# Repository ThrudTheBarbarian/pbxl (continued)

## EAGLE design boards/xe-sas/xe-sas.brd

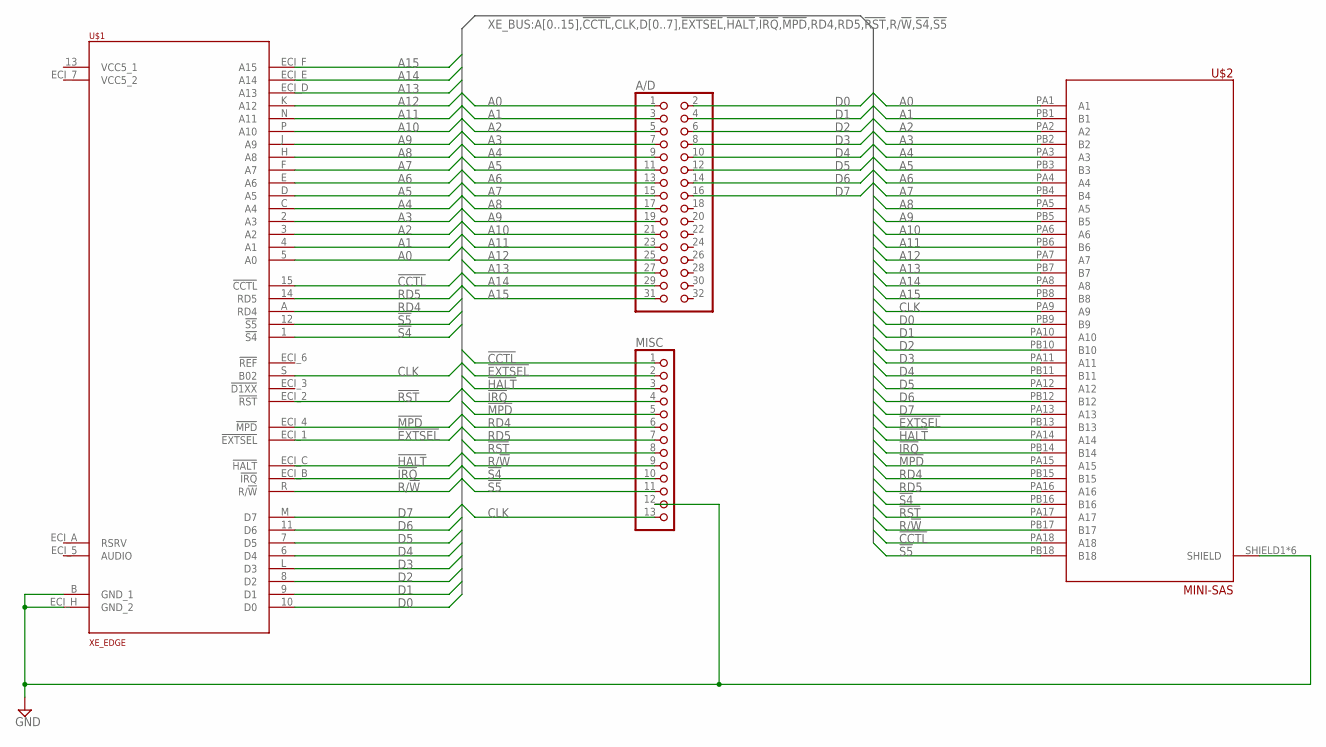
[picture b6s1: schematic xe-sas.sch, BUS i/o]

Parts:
A/D: PINHD-2X16; 2X16
MISC: PINHD-1X13; 1X13
U$1: XE_EDGE
U$2: MINI-SAS

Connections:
!CCTL!: MISC.1, U$1.15 (!CCTL!), U$2.PA18 (A18)
!EXTSEL!: MISC.2, U$1.ECI_1 (!EXTSEL!), U$2.PB13 (B13)
!HALT!: MISC.3, U$1.ECI_C (!HALT!), U$2.PA14 (A14)
!IRQ!: MISC.4, U$1.ECI_B (!IRQ!), U$2.PB14 (B14)
!MPD!: MISC.5, U$1.ECI_4 (!MPD!), U$2.PA15 (A15)
!RST!: MISC.8, U$1.ECI_2 (!RST!), U$2.PA17 (A17)
!S4!: MISC.10, U$1.1 (!S4!), U$2.PB16 (B16)
!S5!: MISC.11, U$1.12 (!S5!), U$2.PB18 (B18)
A0: A/D.1, U$1.5 (A0), U$2.PA1 (A1)
A1: A/D.3, U$1.4 (A1), U$2.PB1 (B1)
A2: A/D.5, U$1.3 (A2), U$2.PA2 (A2)
A3: A/D.7, U$1.2 (A3), U$2.PB2 (B2)
A4: A/D.9, U$1.C (A4), U$2.PA3 (A3)
A5: A/D.11, U$1.D (A5), U$2.PB3 (B3)
A6: A/D.13, U$1.E (A6), U$2.PA4 (A4)
A7: A/D.15, U$1.F (A7), U$2.PB4 (B4)
A8: A/D.17, U$1.H (A8), U$2.PA5 (A5)
A9: A/D.19, U$1.J (A9), U$2.PB5 (B5)
A10: A/D.21, U$1.P (A10), U$2.PA6 (A6)
A11: A/D.23, U$1.N (A11), U$2.PB6 (B6)
A12: A/D.25, U$1.K (A12), U$2.PA7 (A7)
A13: A/D.27, U$1.ECI_D (A13), U$2.PB7 (B7)
A14: A/D.29, U$1.ECI_E (A14), U$2.PA8 (A8)
A15: A/D.31, U$1.ECI_F (A15), U$2.PB8 (B8)
CLK: MISC.13, U$1.S (B02), U$2.PA9 (A9)
D0: A/D.2, U$1.10 (D0), U$2.PB9 (B9)
D1: A/D.4, U$1.9 (D1), U$2.PA10 (A10)
D2: A/D.6, U$1.8 (D2), U$2.PB10 (B10)
D3: A/D.8, U$1.L (D3), U$2.PA11 (A11)
D4: A/D.10, U$1.6 (D4), U$2.PB11 (B11)
D5: A/D.12, U$1.7 (D5), U$2.PA12 (A12)
D6: A/D.14, U$1.11 (D6), U$2.PB12 (B12)
D7: A/D.16, U$1.M (D7), U$2.PA13 (A13)
GND: MISC.12, U$1.B (GND_1), U$1.ECI_H (GND_2), U$2.SHIELD1 (SHIELD), U$2.SHIELD2 (SHIELD), U$2.SHIELD3 (SHIELD), U$2.SHIELD4 (SHIELD), U$2.SHIELD5 (SHIELD), U$2.SHIELD6 (SHIELD)
R/!W!: MISC.9, U$1.R (R/!W!), U$2.PB17 (B17)
RD4: MISC.6, U$1.A (RD4), U$2.PB15 (B15)
RD5: MISC.7, U$1.14 (RD5), U$2.PA16 (A16)

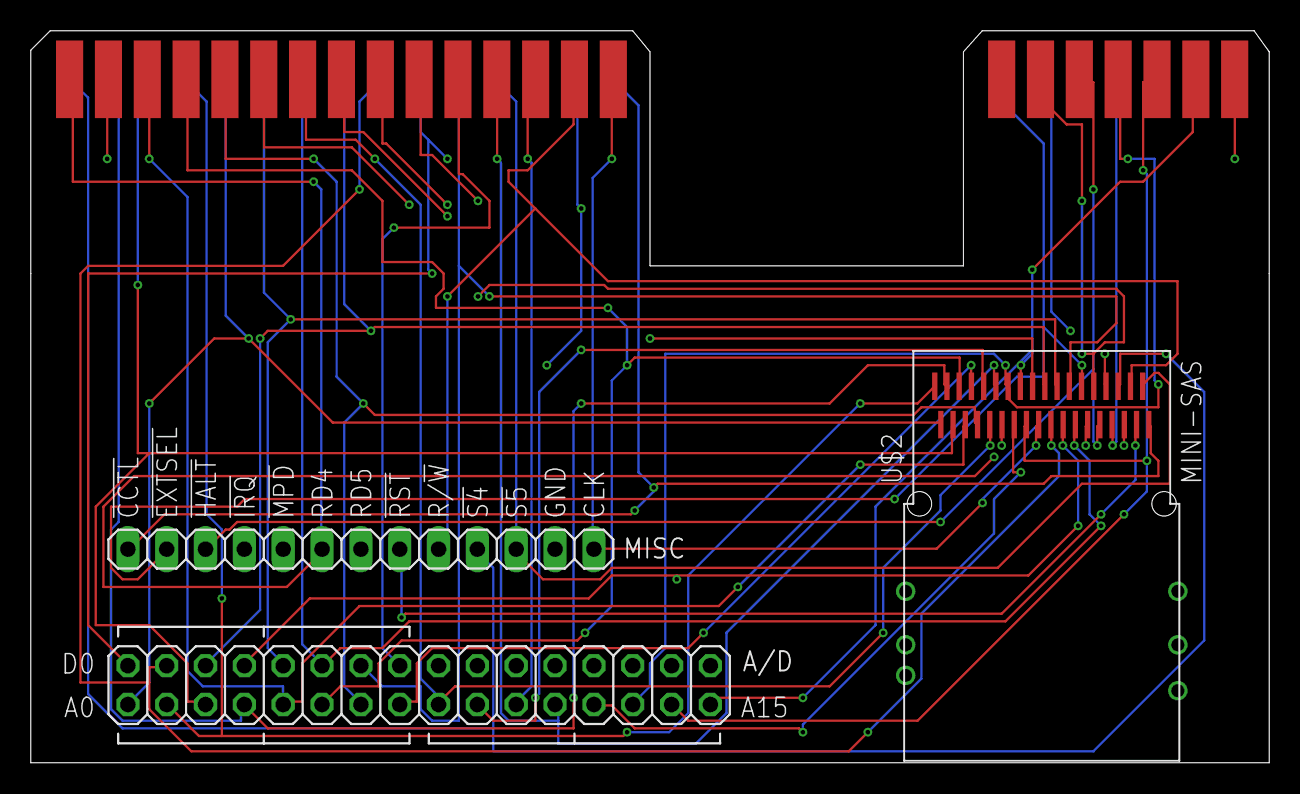
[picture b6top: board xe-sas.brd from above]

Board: 4 copper layers, 81.0 x 47.9 mm, 4 parts (0 on the bottom side), 37 nets.

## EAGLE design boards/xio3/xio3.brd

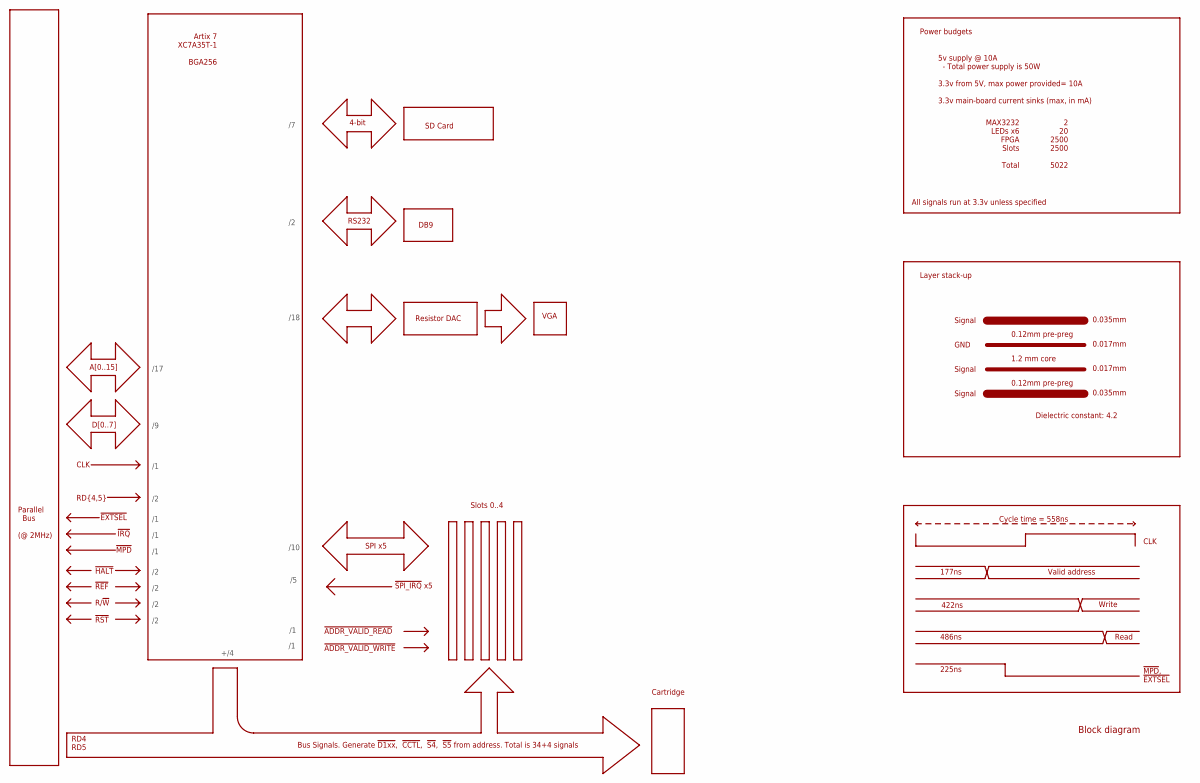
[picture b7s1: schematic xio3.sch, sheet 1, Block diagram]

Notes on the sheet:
Slots 0..4
Bus Signals. Generate !D1xx!, !CCTL!, !S4!, !S5! from address. Total is 34+4 signals
RS232
SD Card
DB9
5v supply @ 10A - Total power supply is 50W 3.3v from 5V, max power provided= 10A 3.3v main-board current sinks (max, in mA)
MAX3232 LEDs x6 FPGA Slots Total
2 20 2500 2500 5022
1.2 mm core
0.12mm pre-preg
0.035mm
0.017mm
Layer stack-up
GND
Dielectric constant: 4.2
Cycle time = 558ns
Valid address
Write
Read
177ns
422ns
486ns
225ns
!MPD!, !EXTSEL!
CLK
Power budgets
Artix 7 XC7A35T-1 BGA256
Resistor DAC
VGA
4-bit
Signal
Block diagram
Parallel Bus (@ 2MHz)
A[0..15]
D[0..7]
RD{4,5}
!MPD!
!IRQ!
!EXTSEL!
!HALT!

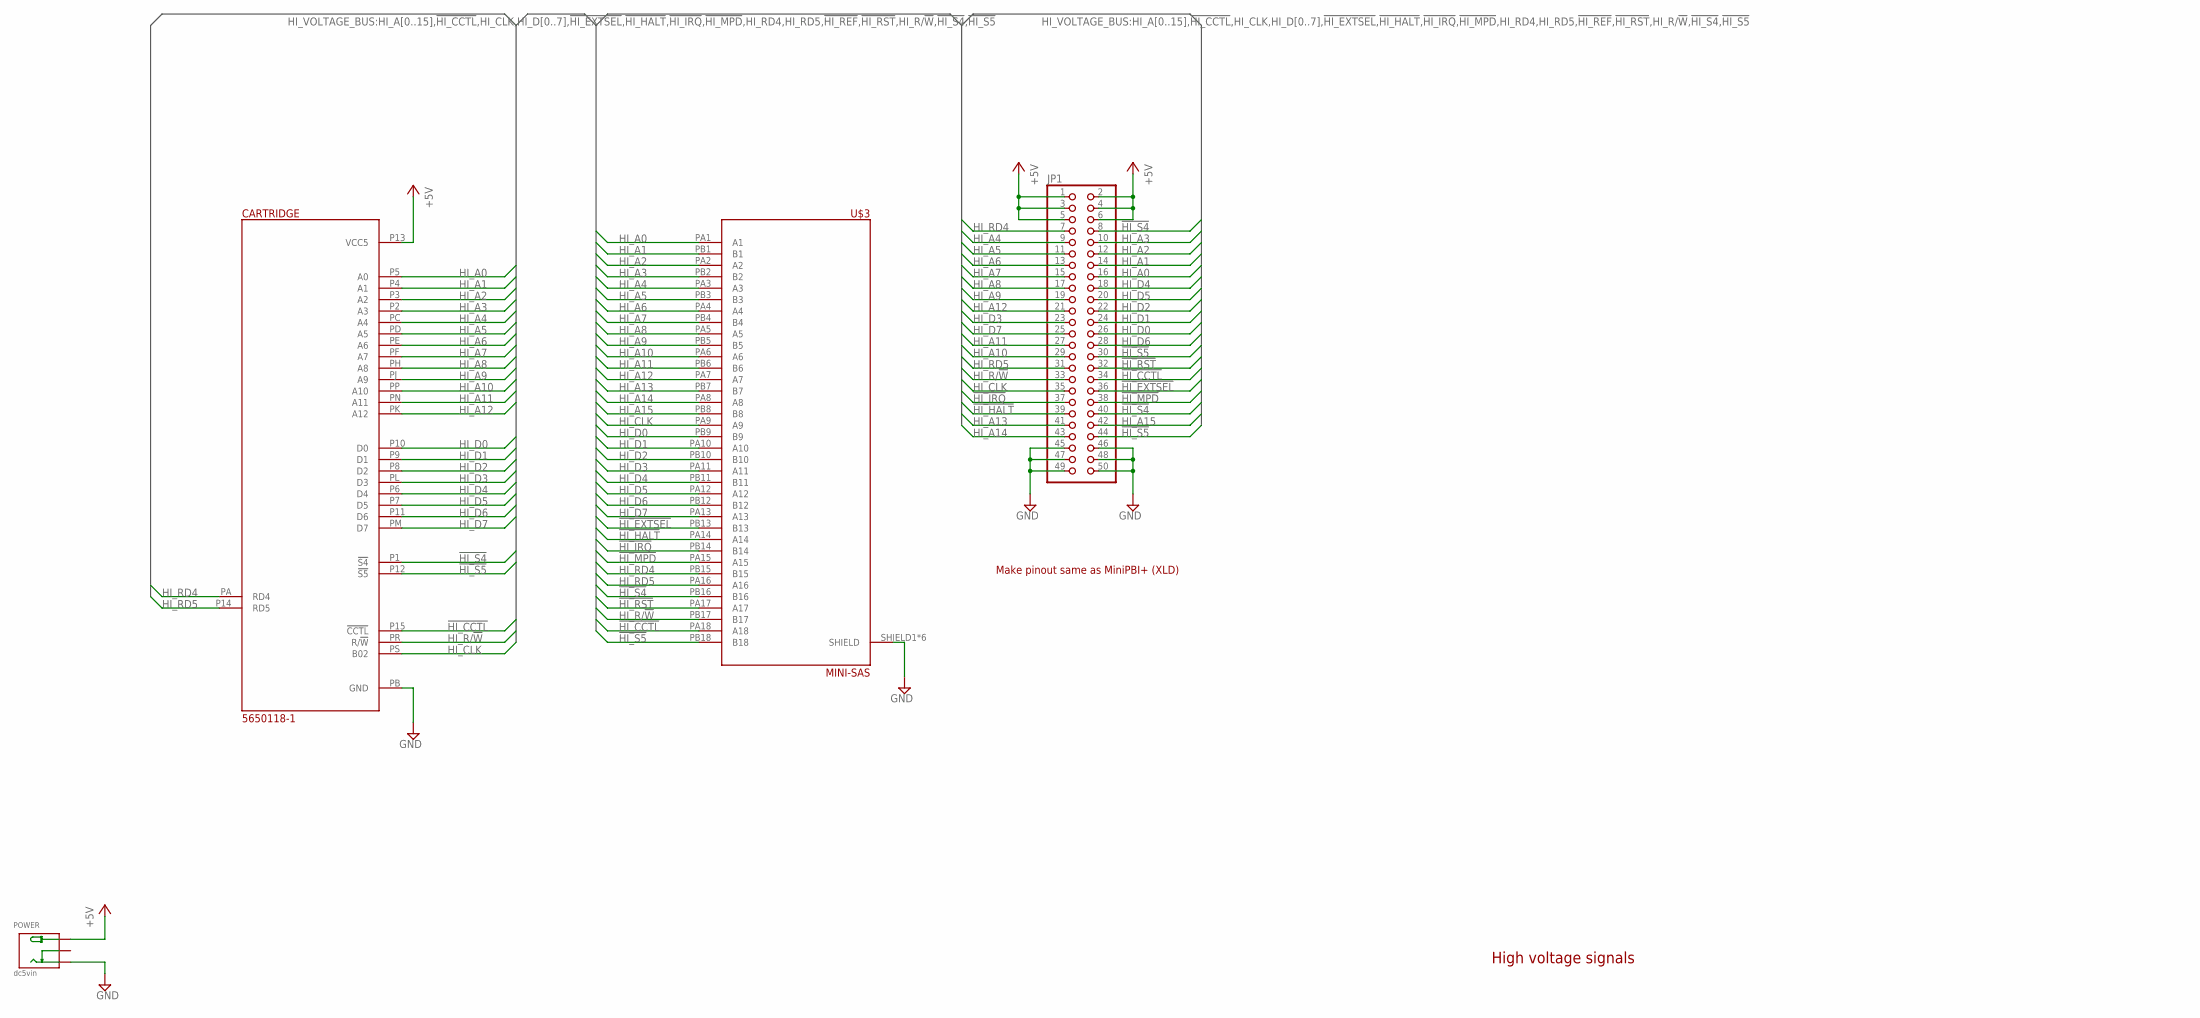
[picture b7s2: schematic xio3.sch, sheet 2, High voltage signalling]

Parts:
CARTRIDGE: 5650118-1; A8_CART
JP1: PINHD-2X25; 2X25
POWER: dc5vin; DCJ3P-14.2X11.0X9.0MM
U$3: MINI-SAS

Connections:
!HI_CCTL!: CARTRIDGE.P15 (!CCTL!), JP1.34, U$3.PA18 (A18)
!HI_EXTSEL!: JP1.36, U$3.PB13 (B13); also elsewhere on the board
!HI_HALT!: JP1.39, U$3.PA14 (A14); also elsewhere on the board
!HI_IRQ!: JP1.37, U$3.PB14 (B14); also elsewhere on the board
!HI_MPD!: JP1.38, U$3.PA15 (A15); also elsewhere on the board
!HI_RST!: JP1.32, U$3.PA17 (A17); also elsewhere on the board
!HI_S4!: CARTRIDGE.P1 (!S4!), JP1.8, JP1.40, U$3.PB16 (B16)
!HI_S5!: CARTRIDGE.P12 (!S5!), JP1.30, JP1.44, U$3.PB18 (B18)
+5V: CARTRIDGE.P13 (VCC5), JP1.1, JP1.2, JP1.3, JP1.4, JP1.5, JP1.6, POWER.+; also elsewhere on the board
GND: CARTRIDGE.PB (GND), JP1.45, JP1.46, JP1.47, JP1.48, JP1.49, JP1.50, POWER.-1 (-), U$3.SHIELD1 (SHIELD), U$3.SHIELD2 (SHIELD), U$3.SHIELD3 (SHIELD), U$3.SHIELD4 (SHIELD), U$3.SHIELD5 (SHIELD), U$3.SHIELD6 (SHIELD); also elsewhere on the board
HI_A0: CARTRIDGE.P5 (A0), JP1.16, U$3.PA1 (A1); also elsewhere on the board
HI_A1: CARTRIDGE.P4 (A1), JP1.14, U$3.PB1 (B1); also elsewhere on the board
HI_A2: CARTRIDGE.P3 (A2), JP1.12, U$3.PA2 (A2); also elsewhere on the board
HI_A3: CARTRIDGE.P2 (A3), JP1.10, U$3.PB2 (B2); also elsewhere on the board
HI_A4: CARTRIDGE.PC (A4), JP1.9, U$3.PA3 (A3); also elsewhere on the board
HI_A5: CARTRIDGE.PD (A5), JP1.11, U$3.PB3 (B3); also elsewhere on the board
HI_A6: CARTRIDGE.PE (A6), JP1.13, U$3.PA4 (A4); also elsewhere on the board
HI_A7: CARTRIDGE.PF (A7), JP1.15, U$3.PB4 (B4); also elsewhere on the board
HI_A8: CARTRIDGE.PH (A8), JP1.17, U$3.PA5 (A5); also elsewhere on the board
HI_A9: CARTRIDGE.PJ (A9), JP1.19, U$3.PB5 (B5); also elsewhere on the board
HI_A10: CARTRIDGE.PP (A10), JP1.29, U$3.PA6 (A6); also elsewhere on the board
HI_A11: CARTRIDGE.PN (A11), JP1.27, U$3.PB6 (B6); also elsewhere on the board
HI_A12: CARTRIDGE.PK (A12), JP1.21, U$3.PA7 (A7); also elsewhere on the board
HI_A13: JP1.41, U$3.PB7 (B7); also elsewhere on the board
HI_A14: JP1.43, U$3.PA8 (A8); also elsewhere on the board
HI_A15: JP1.42, U$3.PB8 (B8); also elsewhere on the board
HI_CLK: CARTRIDGE.PS (B02), JP1.35, U$3.PA9 (A9); also elsewhere on the board
HI_D0: CARTRIDGE.P10 (D0), JP1.26, U$3.PB9 (B9); also elsewhere on the board
HI_D1: CARTRIDGE.P9 (D1), JP1.24, U$3.PA10 (A10); also elsewhere on the board
HI_D2: CARTRIDGE.P8 (D2), JP1.22, U$3.PB10 (B10); also elsewhere on the board
HI_D3: CARTRIDGE.PL (D3), JP1.23, U$3.PA11 (A11); also elsewhere on the board
HI_D4: CARTRIDGE.P6 (D4), JP1.18, U$3.PB11 (B11); also elsewhere on the board
HI_D5: CARTRIDGE.P7 (D5), JP1.20, U$3.PA12 (A12); also elsewhere on the board
HI_D6: CARTRIDGE.P11 (D6), JP1.28, U$3.PB12 (B12); also elsewhere on the board
HI_D7: CARTRIDGE.PM (D7), JP1.25, U$3.PA13 (A13); also elsewhere on the board
HI_R/!W!: CARTRIDGE.PR (R/!W!), JP1.33, U$3.PB17 (B17); also elsewhere on the board
HI_RD4: CARTRIDGE.PA (RD4), JP1.7, U$3.PB15 (B15); also elsewhere on the board
HI_RD5: CARTRIDGE.P14 (RD5), JP1.31, U$3.PA16 (A16); also elsewhere on the board

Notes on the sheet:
High voltage signals
Make pinout same as MiniPBI+ (XLD)

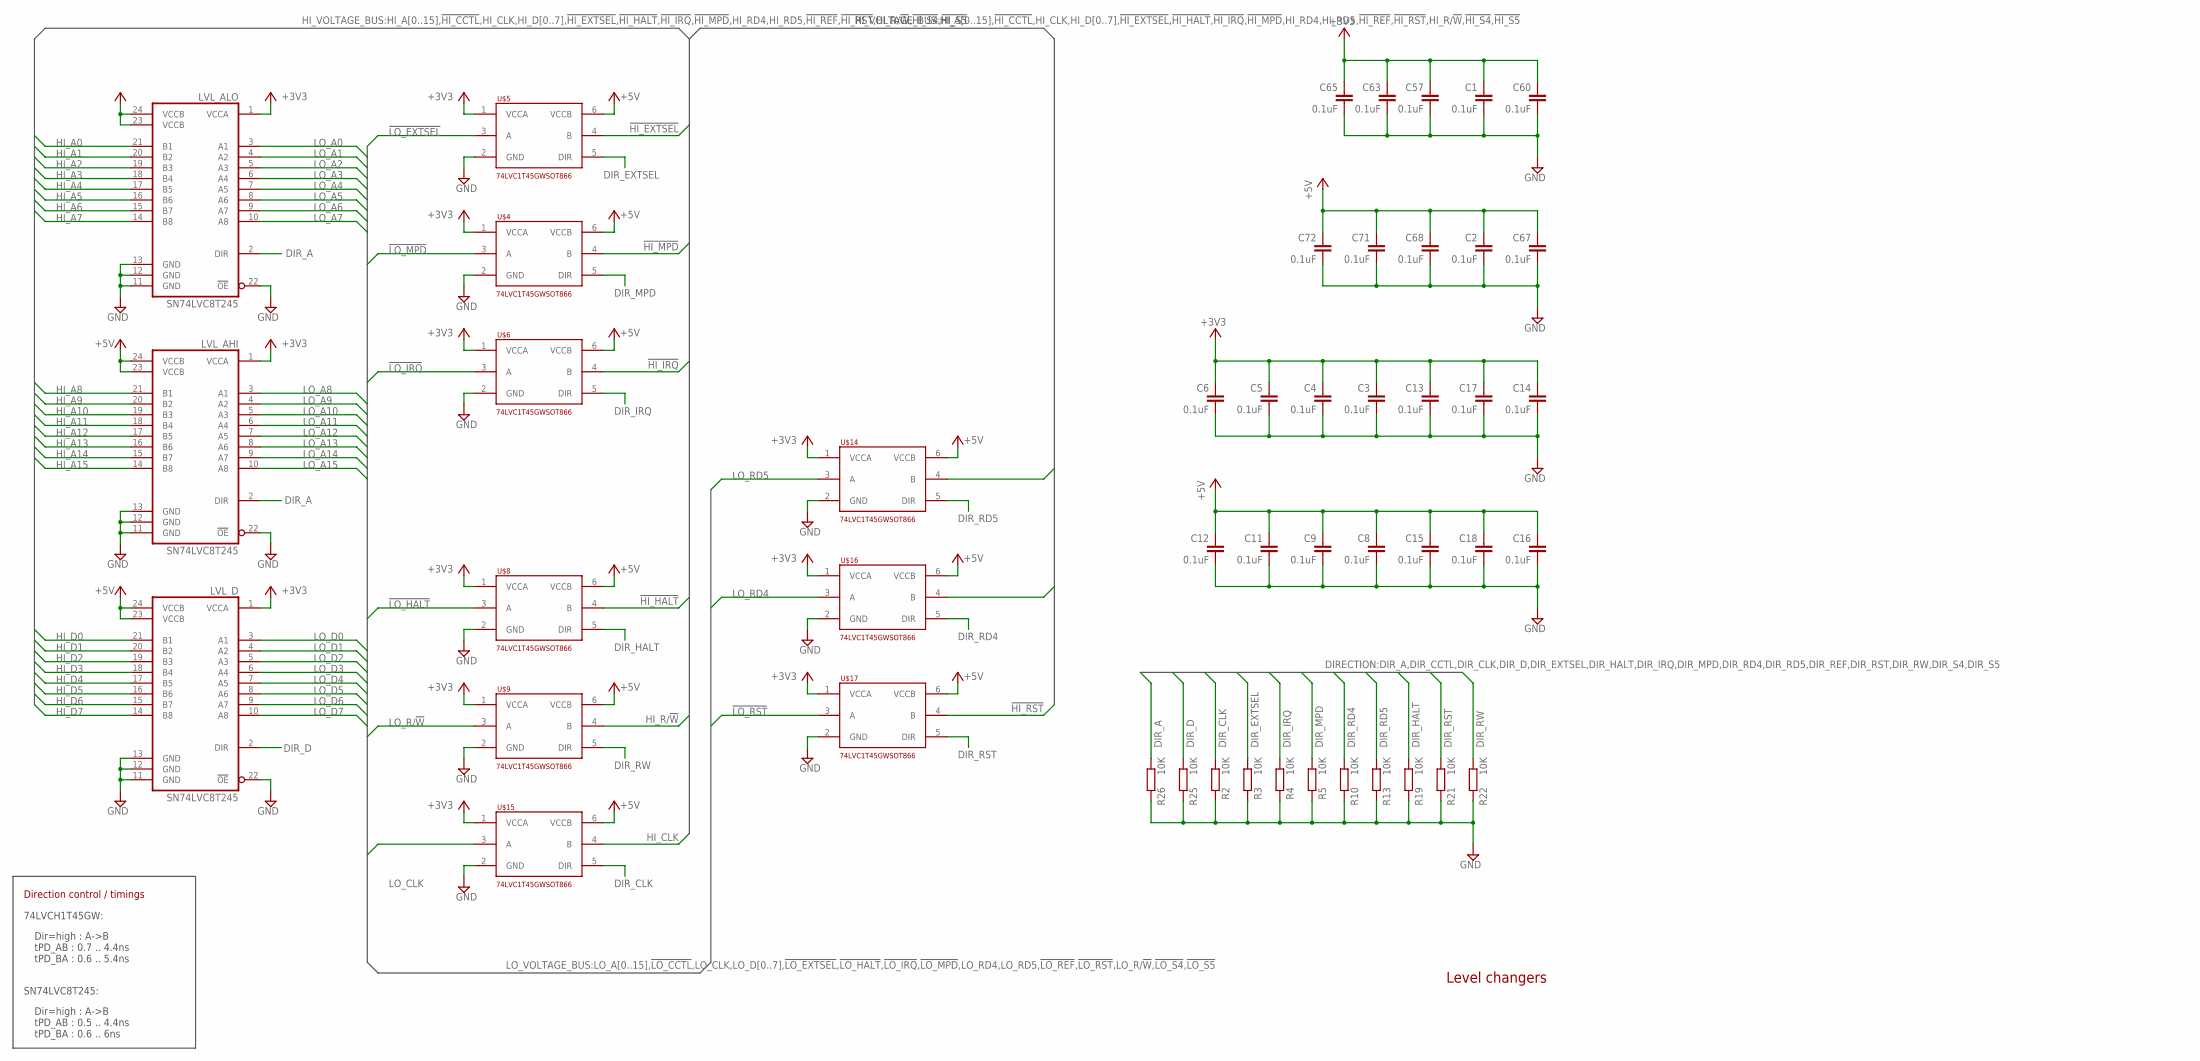
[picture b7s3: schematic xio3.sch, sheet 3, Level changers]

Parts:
C1, C2, C3, C4, C5, C6, C8, C9, C11, C12, C13, C14, C15, C16, C17, C18, C57, C60, C63, C65, C67, C68, C71, C72: 0.1uF; C0201
LVL_AHI: SN74LVC8T245; TSSOP24
LVL_ALO: SN74LVC8T245; TSSOP24
LVL_D: SN74LVC8T245; TSSOP24
R2, R3, R4, R5, R10, R13, R19, R21, R22, R25, R26: 10K; R0201
U$4, U$5, U$6, U$8, U$9, U$14, U$15, U$16, U$17: 74LVC1T45GWSOT866; SOT886

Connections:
!HI_EXTSEL!: U$5.4 (B); also elsewhere on the board
!HI_HALT!: U$8.4 (B); also elsewhere on the board
!HI_IRQ!: U$6.4 (B); also elsewhere on the board
!HI_MPD!: U$4.4 (B); also elsewhere on the board
!HI_RST!: U$17.4 (B); also elsewhere on the board
!LO_EXTSEL!: U$5.3 (A); also elsewhere on the board
!LO_HALT!: U$8.3 (A); also elsewhere on the board
!LO_IRQ!: U$6.3 (A); also elsewhere on the board
!LO_MPD!: U$4.3 (A); also elsewhere on the board
!LO_RST!: U$17.3 (A); also elsewhere on the board
+3V3: C1.1, C3.1, C4.1, C5.1, C6.1, C13.1, C14.1, C17.1, C57.1, C60.1, C63.1, C65.1, LVL_AHI.1 (VCCA), LVL_ALO.1 (VCCA), LVL_D.1 (VCCA), U$4.1 (VCCA), U$5.1 (VCCA), U$6.1 (VCCA), U$8.1 (VCCA), U$9.1 (VCCA), U$14.1 (VCCA), U$15.1 (VCCA), U$16.1 (VCCA), U$17.1 (VCCA); also elsewhere on the board
+5V: C2.1, C8.1, C9.1, C11.1, C12.1, C15.1, C16.1, C18.1, C67.1, C68.1, C71.1, C72.1, LVL_AHI.23 (VCCB), LVL_AHI.24 (VCCB), LVL_ALO.23 (VCCB), LVL_ALO.24 (VCCB), LVL_D.23 (VCCB), LVL_D.24 (VCCB), U$4.6 (VCCB), U$5.6 (VCCB), U$6.6 (VCCB), U$8.6 (VCCB), U$9.6 (VCCB), U$14.6 (VCCB), U$15.6 (VCCB), U$16.6 (VCCB), U$17.6 (VCCB); also elsewhere on the board
DIR_A: LVL_AHI.2 (DIR), LVL_ALO.2 (DIR), R26.1; also elsewhere on the board
DIR_CLK: R2.1, U$15.5 (DIR); also elsewhere on the board
DIR_D: LVL_D.2 (DIR), R25.1; also elsewhere on the board
DIR_EXTSEL: R3.1, U$5.5 (DIR); also elsewhere on the board
DIR_HALT: R19.1, U$8.5 (DIR); also elsewhere on the board
DIR_IRQ: R4.1, U$6.5 (DIR); also elsewhere on the board
DIR_MPD: R5.1, U$4.5 (DIR); also elsewhere on the board
DIR_RD4: R10.1, U$16.5 (DIR); also elsewhere on the board
DIR_RD5: R13.1, U$14.5 (DIR); also elsewhere on the board
DIR_RST: R21.1, U$17.5 (DIR); also elsewhere on the board
DIR_RW: R22.1, U$9.5 (DIR); also elsewhere on the board
GND: C1.2, C2.2, C3.2, C4.2, C5.2, C6.2, C8.2, C9.2, C11.2, C12.2, C13.2, C14.2, C15.2, C16.2, C17.2, C18.2, C57.2, C60.2, C63.2, C65.2, C67.2, C68.2, C71.2, C72.2, LVL_AHI.11 (GND), LVL_AHI.12 (GND), LVL_AHI.13 (GND), LVL_AHI.22 (!OE!), LVL_ALO.11 (GND), LVL_ALO.12 (GND), LVL_ALO.13 (GND), LVL_ALO.22 (!OE!), LVL_D.11 (GND), LVL_D.12 (GND), LVL_D.13 (GND), LVL_D.22 (!OE!), R2.2, R3.2, R4.2, R5.2, R10.2, R13.2, R19.2, R21.2, R22.2, R25.2, R26.2, U$4.2 (GND), U$5.2 (GND), U$6.2 (GND), U$8.2 (GND), U$9.2 (GND), U$14.2 (GND), U$15.2 (GND), U$16.2 (GND), U$17.2 (GND); also elsewhere on the board
HI_A0: LVL_ALO.21 (B1); also elsewhere on the board
HI_A1: LVL_ALO.20 (B2); also elsewhere on the board
HI_A2: LVL_ALO.19 (B3); also elsewhere on the board
HI_A3: LVL_ALO.18 (B4); also elsewhere on the board
HI_A4: LVL_ALO.17 (B5); also elsewhere on the board
HI_A5: LVL_ALO.16 (B6); also elsewhere on the board
HI_A6: LVL_ALO.15 (B7); also elsewhere on the board
HI_A7: LVL_ALO.14 (B8); also elsewhere on the board
HI_A8: LVL_AHI.21 (B1); also elsewhere on the board
HI_A9: LVL_AHI.20 (B2); also elsewhere on the board
HI_A10: LVL_AHI.19 (B3); also elsewhere on the board
HI_A11: LVL_AHI.18 (B4); also elsewhere on the board
HI_A12: LVL_AHI.17 (B5); also elsewhere on the board
HI_A13: LVL_AHI.16 (B6); also elsewhere on the board
HI_A14: LVL_AHI.15 (B7); also elsewhere on the board
HI_A15: LVL_AHI.14 (B8); also elsewhere on the board
HI_CLK: U$15.4 (B); also elsewhere on the board
HI_D0: LVL_D.21 (B1); also elsewhere on the board
HI_D1: LVL_D.20 (B2); also elsewhere on the board
HI_D2: LVL_D.19 (B3); also elsewhere on the board
HI_D3: LVL_D.18 (B4); also elsewhere on the board
HI_D4: LVL_D.17 (B5); also elsewhere on the board
HI_D5: LVL_D.16 (B6); also elsewhere on the board
HI_D6: LVL_D.15 (B7); also elsewhere on the board
HI_D7: LVL_D.14 (B8); also elsewhere on the board
HI_R/!W!: U$9.4 (B); also elsewhere on the board
HI_RD4: U$16.4 (B); also elsewhere on the board
HI_RD5: U$14.4 (B); also elsewhere on the board
LO_A0: LVL_ALO.3 (A1); also elsewhere on the board
LO_A1: LVL_ALO.4 (A2); also elsewhere on the board
LO_A2: LVL_ALO.5 (A3); also elsewhere on the board
LO_A3: LVL_ALO.6 (A4); also elsewhere on the board
LO_A4: LVL_ALO.7 (A5); also elsewhere on the board
LO_A5: LVL_ALO.8 (A6); also elsewhere on the board
LO_A6: LVL_ALO.9 (A7); also elsewhere on the board
LO_A7: LVL_ALO.10 (A8); also elsewhere on the board
LO_A8: LVL_AHI.3 (A1); also elsewhere on the board
LO_A9: LVL_AHI.4 (A2); also elsewhere on the board
LO_A10: LVL_AHI.5 (A3); also elsewhere on the board
LO_A11: LVL_AHI.6 (A4); also elsewhere on the board
LO_A12: LVL_AHI.7 (A5); also elsewhere on the board
LO_A13: LVL_AHI.8 (A6); also elsewhere on the board
LO_A14: LVL_AHI.9 (A7); also elsewhere on the board
LO_A15: LVL_AHI.10 (A8); also elsewhere on the board
LO_CLK: U$15.3 (A); also elsewhere on the board
LO_D0: LVL_D.3 (A1); also elsewhere on the board
LO_D1: LVL_D.4 (A2); also elsewhere on the board
LO_D2: LVL_D.5 (A3); also elsewhere on the board
LO_D3: LVL_D.6 (A4); also elsewhere on the board
LO_D4: LVL_D.7 (A5); also elsewhere on the board
LO_D5: LVL_D.8 (A6); also elsewhere on the board
LO_D6: LVL_D.9 (A7); also elsewhere on the board
LO_D7: LVL_D.10 (A8); also elsewhere on the board
LO_R/!W!: U$9.3 (A); also elsewhere on the board
LO_RD4: U$16.3 (A); also elsewhere on the board
LO_RD5: U$14.3 (A); also elsewhere on the board

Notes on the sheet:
Dir=high : A->B tPD_AB : 0.7 .. 4.4ns tPD_BA : 0.6 .. 5.4ns
74LVCH1T45GW:
SN74LVC8T245:
Dir=high : A->B tPD_AB : 0.5 .. 4.4ns tPD_BA : 0.6 .. 6ns
Direction control / timings
Level changers

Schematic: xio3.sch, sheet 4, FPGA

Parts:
H3, H6, H7, H8: MOUNT-HOLE4.1; 4,1
JP3: PINHD-2X10; 2X10
U$1: QM_A35T; QMTECH

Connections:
!LO_EXTSEL!: U$1.U7_43 (BANK14_N6); also elsewhere on the board
!LO_HALT!: U$1.U7_44 (BANK14_M6); also elsewhere on the board
!LO_IRQ!: U$1.U7_45 (BANK34_L5); also elsewhere on the board
!LO_MPD!: U$1.U7_46 (BANK34_P5); also elsewhere on the board
!LO_RST!: U$1.U7_49 (BANK34_R3); also elsewhere on the board
+3V3: JP3.1, U$1.U7_3 (3V3), U$1.U7_4 (3V3), U$1.U8_3 (VCCO_34_35), U$1.U8_4 (VCCO_34_35); also elsewhere on the board
+5V: JP3.2, U$1.U7_63 (VIN), U$1.U7_64 (VIN), U$1.U8_63 (VIN), U$1.U8_64 (VIN); also elsewhere on the board
DIR_A: U$1.U7_55 (BANK34_P4); also elsewhere on the board
DIR_CCTL: U$1.U7_56 (BANK34_P3)
DIR_CLK: U$1.U7_57 (BANK34_N1); also elsewhere on the board
DIR_D: U$1.U7_58 (BANK34_P1); also elsewhere on the board
DIR_EXTSEL: U$1.U7_59 (BANK34_M2); also elsewhere on the board
DIR_HALT: U$1.U7_60 (BANK34_M1); also elsewhere on the board
DIR_IRQ: U$1.U8_7 (BANK35_B7); also elsewhere on the board
DIR_MPD: U$1.U8_8 (BANK35_A7); also elsewhere on the board
DIR_RD4: U$1.U8_9 (BANK35_B6); also elsewhere on the board
DIR_RD5: U$1.U8_10 (BANK35_B5); also elsewhere on the board
DIR_REF: U$1.U8_11 (BANK35_E6)
DIR_RST: U$1.U8_12 (BANK35_K5); also elsewhere on the board
DIR_RW: U$1.U8_13 (BANK35_J5); also elsewhere on the board
DIR_S4: U$1.U8_14 (BANK35_J4)
DIR_S5: U$1.U8_15 (BANK35_G5)
GND: JP3.17, JP3.18, JP3.19, JP3.20, U$1.U7_1 (GND), U$1.U7_2 (GND), U$1.U7_5 (GND), U$1.U7_6 (GND), U$1.U7_61 (GND), U$1.U7_62 (GND), U$1.U8_1 (GND), U$1.U8_2 (GND), U$1.U8_5 (GND), U$1.U8_6 (GND), U$1.U8_61 (GND), U$1.U8_62 (GND); also elsewhere on the board
HBUS0: JP3.3, U$1.U8_42 (BANK35_F3); also elsewhere on the board
HBUS1: JP3.4, U$1.U8_41 (BANK35_F4); also elsewhere on the board
HBUS2: JP3.5, U$1.U8_40 (BANK35_E1); also elsewhere on the board
HBUS3: JP3.6, U$1.U8_39 (BANK35_F2); also elsewhere on the board
HBUS4: JP3.7, U$1.U8_38 (BANK35_E5); also elsewhere on the board
HBUS5: JP3.8, U$1.U8_37 (BANK35_F5); also elsewhere on the board
HBUS6: JP3.9, U$1.U8_36 (BANK35_D3); also elsewhere on the board
HBUS7: JP3.10, U$1.U8_35 (BANK35_E3); also elsewhere on the board
HBUS8: JP3.11, U$1.U8_34 (BANK35_D1); also elsewhere on the board
HBUS9: JP3.12, U$1.U8_33 (BANK35_E2); also elsewhere on the board
HBUS10: JP3.13, U$1.U7_51 (BANK34_R2); also elsewhere on the board
HBUS11: JP3.14, U$1.U7_52 (BANK34_R1); also elsewhere on the board
HBUS12: JP3.15, U$1.U7_53 (BANK34_M5); also elsewhere on the board
HBUS13: JP3.16, U$1.U7_54 (BANK34_N4); also elsewhere on the board
LO_A0: U$1.U7_18 (BANK14_P14); also elsewhere on the board
LO_A1: U$1.U7_19 (BANK14_T13); also elsewhere on the board
LO_A2: U$1.U7_20 (BANK14_R13); also elsewhere on the board
LO_A3: U$1.U7_21 (BANK14_T12); also elsewhere on the board
LO_A4: U$1.U7_22 (BANK14_R12); also elsewhere on the board
LO_A5: U$1.U7_23 (BANK14_L13); also elsewhere on the board
LO_A6: U$1.U7_24 (BANK14_N12); also elsewhere on the board
LO_A7: U$1.U7_25 (BANK14_K12); also elsewhere on the board
LO_A8: U$1.U7_26 (BANK14_K13); also elsewhere on the board
LO_A9: U$1.U7_27 (BANK14_P10); also elsewhere on the board
LO_A10: U$1.U7_28 (BANK14_P11); also elsewhere on the board
LO_A11: U$1.U7_29 (BANK14_N9); also elsewhere on the board
LO_A12: U$1.U7_30 (BANK14_P9); also elsewhere on the board
LO_A13: U$1.U7_31 (BANK14_T10); also elsewhere on the board
LO_A14: U$1.U7_32 (BANK14_R11); also elsewhere on the board
LO_A15: U$1.U7_33 (BANK14_T9); also elsewhere on the board
LO_CLK: U$1.U7_34 (BANK14_R10); also elsewhere on the board
LO_D0: U$1.U7_35 (BANK14_T8); also elsewhere on the board
LO_D1: U$1.U7_36 (BANK14_R8); also elsewhere on the board
LO_D2: U$1.U7_37 (BANK14_T7); also elsewhere on the board
LO_D3: U$1.U7_38 (BANK14_R7); also elsewhere on the board
LO_D4: U$1.U7_39 (BANK14_T5); also elsewhere on the board
LO_D5: U$1.U7_40 (BANK14_R6); also elsewhere on the board
LO_D6: U$1.U7_41 (BANK14_P6); also elsewhere on the board
LO_D7: U$1.U7_42 (BANK14_R5); also elsewhere on the board
LO_R/!W!: U$1.U7_50 (BANK34_T2); also elsewhere on the board
LO_RD4: U$1.U7_47 (BANK34_T4); also elsewhere on the board
LO_RD5: U$1.U7_48 (BANK34_T3); also elsewhere on the board
MCU_CTS: U$1.U7_14 (BANK14_R16); also elsewhere on the board
MCU_RTS: U$1.U7_15 (BANK14_T14); also elsewhere on the board
MCU_RX: U$1.U7_16 (BANK14_T15); also elsewhere on the board
MCU_TX: U$1.U7_17 (BANK14_P13); also elsewhere on the board
SD0: U$1.U7_12 (BANK14_P16); also elsewhere on the board
SD1: U$1.U7_13 (BANK14_R15); also elsewhere on the board
SD2: U$1.U7_7 (BANK14_M12); also elsewhere on the board
SD3: U$1.U7_8 (BANK14_N13); also elsewhere on the board
SDCD: U$1.U7_10 (BANK14_N16); also elsewhere on the board
SDCLK: U$1.U7_11 (BANK14_P15); also elsewhere on the board
SDCMD: U$1.U7_9 (BANK14_N14); also elsewhere on the board
SPI0_IRQ: U$1.U8_16 (BANK35_G4); also elsewhere on the board
SPI0_MOSI: U$1.U8_18 (BANK35_C6); also elsewhere on the board
SPI1_IRQ: U$1.U8_19 (BANK35_D6); also elsewhere on the board
SPI1_MISO: U$1.U8_20 (BANK35_D5); also elsewhere on the board
SPI1_MOSI: U$1.U8_21 (BANK35_A5); also elsewhere on the board
SPI2_IRQ: U$1.U8_22 (BANK35_A4); also elsewhere on the board
SPI2_MISO: U$1.U8_23 (BANK35_B4); also elsewhere on the board
SPI2_MOSI: U$1.U8_24 (BANK35_A3); also elsewhere on the board
SPI3_IRQ: U$1.U8_25 (BANK35_D4); also elsewhere on the board
SPI3_MISO: U$1.U8_26 (BANK35_C4); also elsewhere on the board
SPI3_MOSI: U$1.U8_27 (BANK35_C3); also elsewhere on the board
SPI4_IRQ: U$1.U8_28 (BANK35_C2); also elsewhere on the board
SPI4_MISO: U$1.U8_29 (BANK35_B2); also elsewhere on the board
SPI4_MOSI: U$1.U8_30 (BANK35_A2); also elsewhere on the board
SPIO_MISO: U$1.U8_17 (BANK35_C7); also elsewhere on the board
VALID_RD: U$1.U8_31 (BANK35_C1); also elsewhere on the board
VALID_WR: U$1.U8_32 (BANK35_B1); also elsewhere on the board
VGA_B0: U$1.U8_49 (BANK35_L3); also elsewhere on the board
VGA_B1: U$1.U8_47 (BANK35_K1); also elsewhere on the board
VGA_B2: U$1.U8_48 (BANK35_J1); also elsewhere on the board
VGA_B3: U$1.U8_45 (BANK35_H2); also elsewhere on the board
VGA_B4: U$1.U8_46 (BANK35_H1); also elsewhere on the board
VGA_G0: U$1.U8_55 (BANK35_K3); also elsewhere on the board
VGA_G1: U$1.U8_54 (BANK35_H3); also elsewhere on the board
VGA_G2: U$1.U8_52 (BANK35_H4); also elsewhere on the board
VGA_G3: U$1.U8_53 (BANK35_J3); also elsewhere on the board
VGA_G4: U$1.U8_50 (BANK35_L2); also elsewhere on the board
VGA_G5: U$1.U8_51 (BANK35_H5); also elsewhere on the board
VGA_HSYNC: U$1.U8_44 (BANK35_G1); also elsewhere on the board
VGA_R0: U$1.U8_60 (BANK34_N2); also elsewhere on the board
VGA_R1: U$1.U8_58 (BANK34_M4); also elsewhere on the board
VGA_R2: U$1.U8_59 (BANK34_N3); also elsewhere on the board
VGA_R3: U$1.U8_56 (BANK35_K2); also elsewhere on the board
VGA_R4: U$1.U8_57 (BANK34_L4); also elsewhere on the board
VGA_VSYNC: U$1.U8_43 (BANK35_G2); also elsewhere on the board

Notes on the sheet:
FPGA
Top 7 SD card Next 4 RS232 Next 34 Bus

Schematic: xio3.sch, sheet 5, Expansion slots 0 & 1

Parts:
C53, C54: 0.1uF; C0201
LD_0P1, LD_1P: SML-D12D1WT86; CHIPLED_0603
R27, R98: 59R; R0402
R61, R62: 10K; R0201
SLOT0, SLOT1: PCIE_64; PCI-E_64

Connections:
!LO_CCTL!: SLOT0.A27, SLOT1.A27; also elsewhere on the board
!LO_EXTSEL!: SLOT0.A29, SLOT1.A29; also elsewhere on the board
!LO_HALT!: SLOT0.B13, SLOT1.B13; also elsewhere on the board
!LO_IRQ!: SLOT0.B14, SLOT1.B14; also elsewhere on the board
!LO_MPD!: SLOT0.A30, SLOT1.A30; also elsewhere on the board
!LO_REF!: SLOT0.B15, SLOT1.B15; also elsewhere on the board
!LO_RST!: SLOT0.B16, SLOT1.B16; also elsewhere on the board
+3V3: SLOT1.A3; also elsewhere on the board
+5V: C53.1, C54.1, SLOT0.B1, SLOT0.B2, SLOT0.B3, SLOT1.B1, SLOT1.B2, SLOT1.B3; also elsewhere on the board
GND: C53.2, C54.2, LD_0P1.C, LD_1P.C, R61.1, R62.1, SLOT0.A1, SLOT0.A2, SLOT0.A3, SLOT0.A4, SLOT0.A5, SLOT0.B32, SLOT1.A1, SLOT1.A2, SLOT1.A4, SLOT1.A5, SLOT1.B32; also elsewhere on the board
HBUS0: SLOT0.B18, SLOT1.B18; also elsewhere on the board
HBUS1: SLOT0.B19, SLOT1.B19; also elsewhere on the board
HBUS2: SLOT0.B20, SLOT1.B20; also elsewhere on the board
HBUS3: SLOT0.B21, SLOT1.B21; also elsewhere on the board
HBUS4: SLOT0.B22, SLOT1.B22; also elsewhere on the board
HBUS5: SLOT0.B23, SLOT1.B23; also elsewhere on the board
HBUS6: SLOT0.B24, SLOT1.B24; also elsewhere on the board
HBUS7: SLOT0.B25, SLOT1.B25; also elsewhere on the board
HBUS8: SLOT0.B26, SLOT1.B26; also elsewhere on the board
HBUS9: SLOT0.B27, SLOT1.B27; also elsewhere on the board
HBUS10: SLOT0.B28, SLOT1.B28; also elsewhere on the board
HBUS11: SLOT0.B29, SLOT1.B29; also elsewhere on the board
HBUS12: SLOT0.B30, SLOT1.B30; also elsewhere on the board
HBUS13: SLOT0.B31, SLOT1.B31; also elsewhere on the board
LO_A0: SLOT0.A11, SLOT1.A11; also elsewhere on the board
LO_A1: SLOT0.A12, SLOT1.A12; also elsewhere on the board
LO_A2: SLOT0.A13, SLOT1.A13; also elsewhere on the board
LO_A3: SLOT0.A14, SLOT1.A14; also elsewhere on the board
LO_A4: SLOT0.A15, SLOT1.A15; also elsewhere on the board
LO_A5: SLOT0.A16, SLOT1.A16; also elsewhere on the board
LO_A6: SLOT0.A17, SLOT1.A17; also elsewhere on the board
LO_A7: SLOT0.A18, SLOT1.A18; also elsewhere on the board
LO_A8: SLOT0.A19, SLOT1.A19; also elsewhere on the board
LO_A9: SLOT0.A20, SLOT1.A20; also elsewhere on the board
LO_A10: SLOT0.A21, SLOT1.A21; also elsewhere on the board
LO_A11: SLOT0.A22, SLOT1.A22; also elsewhere on the board
LO_A12: SLOT0.A23, SLOT1.A23; also elsewhere on the board
LO_A13: SLOT0.A24, SLOT1.A24; also elsewhere on the board
LO_A14: SLOT0.A25, SLOT1.A25; also elsewhere on the board
LO_A15: SLOT0.A26, SLOT1.A26; also elsewhere on the board
LO_CLK: SLOT0.A28, SLOT1.A28; also elsewhere on the board
LO_D0: SLOT0.B5, SLOT1.B5; also elsewhere on the board
LO_D1: SLOT0.B6, SLOT1.B6; also elsewhere on the board
LO_D2: SLOT0.B7, SLOT1.B7; also elsewhere on the board
LO_D3: SLOT0.B8, SLOT1.B8; also elsewhere on the board
LO_D4: SLOT0.B9, SLOT1.B9; also elsewhere on the board
LO_D5: SLOT0.B10, SLOT1.B10; also elsewhere on the board
LO_D6: SLOT0.B11, SLOT1.B11; also elsewhere on the board
LO_D7: SLOT0.B12, SLOT1.B12; also elsewhere on the board
LO_R/!W!: SLOT0.B17, SLOT1.B17; also elsewhere on the board
LO_RD4: SLOT0.A31, SLOT1.A31; also elsewhere on the board
LO_RD5: SLOT0.A32, SLOT1.A32; also elsewhere on the board
unnamed: LD_0P1.A, R27.2
unnamed: LD_1P.A, R98.2
S0_PRESENT: R27.1, R61.2, SLOT0.B4
S1_PRESENT: R62.2, R98.1, SLOT1.B4
SPI0_IRQ: SLOT0.A8; also elsewhere on the board
SPI0_MOSI: SLOT0.A9; also elsewhere on the board
SPI1_IRQ: SLOT1.A8; also elsewhere on the board
SPI1_MISO: SLOT1.A10; also elsewhere on the board
SPI1_MOSI: SLOT1.A9; also elsewhere on the board
SPIO_MISO: SLOT0.A10; also elsewhere on the board
VALID_RD: SLOT0.A7, SLOT1.A7; also elsewhere on the board
VALID_WR: SLOT0.A6, SLOT1.A6; also elsewhere on the board

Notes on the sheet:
Slots 0,1
Slot id: 0,0,0
Slot id: 0,0,1
B1,2,3 B4 A1,2,3 A4,5,6,7
+5V Card-present Slot ID GND
Orange LED
Green and Orange LEDs are configured for 20mA current
Amber and Red LEDs are configured for 10mA current
LED resistor values
